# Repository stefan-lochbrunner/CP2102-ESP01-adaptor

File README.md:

# CP2102-ESP01-adaptor

Adaptor PCB to turn a CP2102 USB serial converter into an ESP01 programmer. Shared PCB on [Aisler](https://aisler.net/p/EWJLMEIE).

<br>

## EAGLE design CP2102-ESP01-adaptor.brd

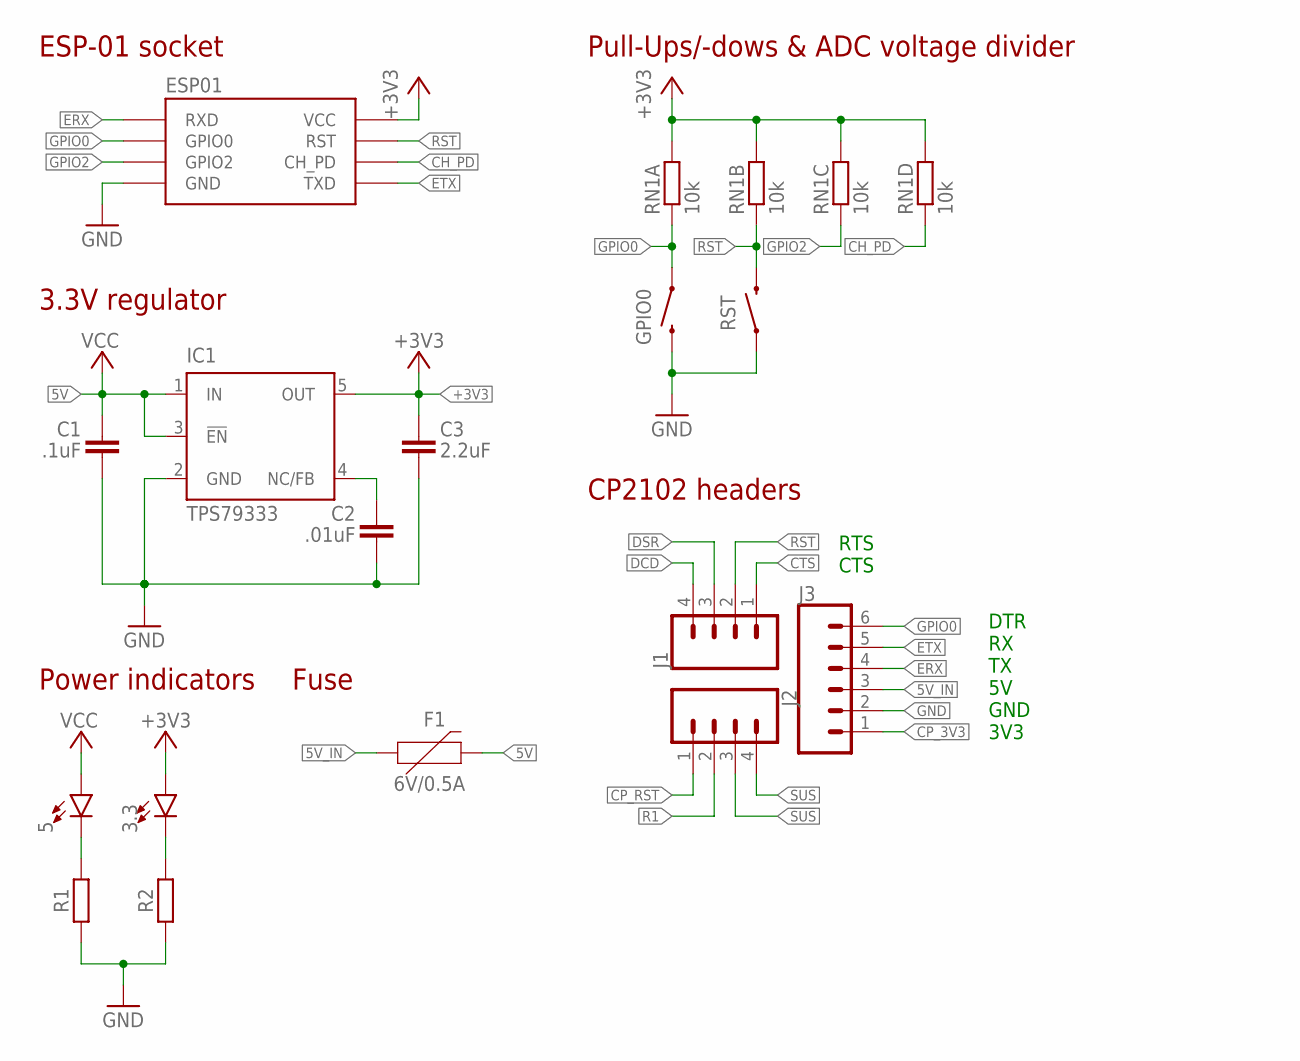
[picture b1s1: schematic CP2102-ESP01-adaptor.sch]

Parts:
3.3, 5: LED0603; LED-0603
C1: .1uF; C603
C2: .01uF; C603
C3: 2.2uF; C603
ESP-01: ESP01
F1: 6V/0.5A; 1206
GPIO0: MOMENTARY-SWITCH-SPST-SMD-RIGHT-ANGLE; TACTILE_SWITCH_SMD_RIGHT_ANGLE
IC1: TPS79333; SOT23-DBV
J1, J2: CONN_04LOCK; 1X04_LOCK
J3: CONN_06LOCK; 1X06_LOCK
R1, R2: 1k; R603
RN1: 10k; RN8P-4R-CRA06S
RST: MOMENTARY-SWITCH-SPST-SMD-RIGHT-ANGLE; TACTILE_SWITCH_SMD_RIGHT_ANGLE

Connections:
5V: 5.A, C1.1, F1.2, IC1.1 (IN), IC1.3 (!EN)
5V_IN: F1.1, J3.3
!SUS: J2.3
+3V3: 3.3.A, C3.1, ESP-01.VCC, IC1.5 (OUT), RN1.5 (2), RN1.6 (2), RN1.7 (2), RN1.8 (2)
BYPASS: C2.1, IC1.4 (NC/FB)
CH_PD: ESP-01.CH_PD, RN1.4 (1)
CP_3V3: J3.1
CP_RST: J2.1
CTS: J1.1
DCD: J1.4
DSR: J1.3
ERX: ESP-01.RX (RXD), J3.4
ETX: ESP-01.TX (TXD), J3.5
GND: C1.2, C2.2, C3.2, ESP-01.GND, GPIO0.2, IC1.2 (GND), J3.2, R1.1, R2.1, RST.1
GPIO0: ESP-01.GPIO0, GPIO0.1, J3.6, RN1.1
GPIO2: ESP-01.GPIO2, RN1.3 (1)
unnamed: 5.C, R1.2
unnamed: 3.3.C, R2.2
R1: J2.2
RST: ESP-01.RST, J1.2, RN1.2 (1), RST.2
SUS: J2.4

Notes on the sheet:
3.3V regulator
Pull-Ups/-dows & ADC voltage divider
ESP-01 socket
CP2102 headers
Power indicators
Fuse
DTR RX TX 5V GND 3V3
RTS CTS

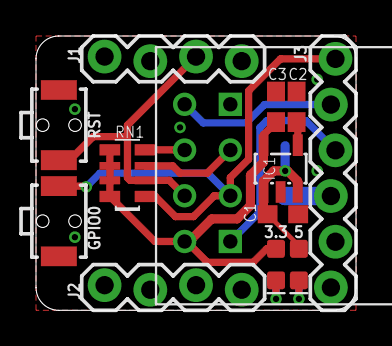
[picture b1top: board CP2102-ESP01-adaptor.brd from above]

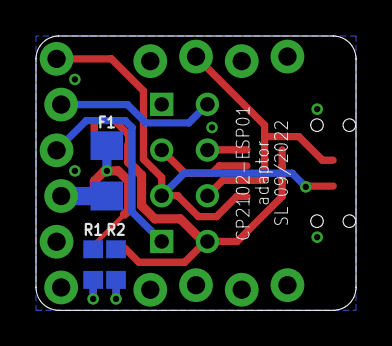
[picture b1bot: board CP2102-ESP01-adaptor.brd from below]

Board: 2 copper layers, 17.8 x 15.2 mm, 16 parts (3 on the bottom side), 13 nets.

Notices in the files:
parts and their libraries:
SparkFun-Switches: Licensing: Creative Commons ShareAlike 4.0 International - https://creativecommons.org/licenses/by-sa/4.0
